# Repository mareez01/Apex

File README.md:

# Project Apex: Mixed-Signal Diagnostic Instrument

Hardware design, manufacturing files, and system architecture for Project Apex, a multi-functional diagnostic edge-computing tool

**Demonstration:**
*   Watch the hardware demo here: https://drive.google.com/drive/folders/1B4_CrYPebX7i6lBTUv4ibxBGYRtsgXC7?usp=sharing

## Version 1.0 (Current Files)
*   **Architecture:** Dual-MCU system featuring an ESP32 master and ATmega328P co-processor.
*   **PCB:** Custom 4-layer stackup engineered to ensure signal integrity by isolating the 3.3V digital logic from the 5V analog domains[cite: 1].
*   **Analog Front-End:** Auto-ranging 12-bit impedance analyzer utilizing an AD9833 waveform generator, MCP6022 PGA, and MCP3208 ADC over an isolated SPI bus.
*   **Digital IC Tester:** 16-pin ZIF socket routed via a discrete 1P3T mechanical switch matrix for deterministic fault injection and truth-table validation.
*   **Project reports are listed:** The Final version 1 project report have been submitted with all the ECAD files and GERBER files.

## Version 2.0 Roadmap (In Development)
Transitioning to a fully autonomous, solid-state architecture to support 24MSPS logic analysis and frequency response plotting (Bode/Nyquist).
*   **Master MCU:** Upgrading to STM32H723 (550MHz) utilizing DMA for high-speed ADC polling and 16-channel logic analysis.
*   **Slave MCU:** Upgrading to AVR32DB48. Utilizes native Multi-Voltage I/O (MVIO) on Port C to eliminate external level shifters. Includes dedicated 12-bit ADC channels for absolute floating-gate fault detection.
*   **Solid-State Matrix:** Replacing mechanical relays with an AO4606/SI1539CDL MOSFET crossbar switching matrix for automated IC power routing.
*   **PC Interface:** Transitioning from serial prints to a Python/PySide6 desktop GUI utilizing pySerial for live PyQtGraph data visualization.
*   **Design Files** So we are actively wroking on the version 2 deisgn and the design documention file is listed here please use iitm mail id to view the G-sheets :https://docs.google.com/document/d/17MV_ibkEd-tFQ1U5sWTHGYrbQkPEoYyiVjMqvgrKTJg/edit?usp=sharing

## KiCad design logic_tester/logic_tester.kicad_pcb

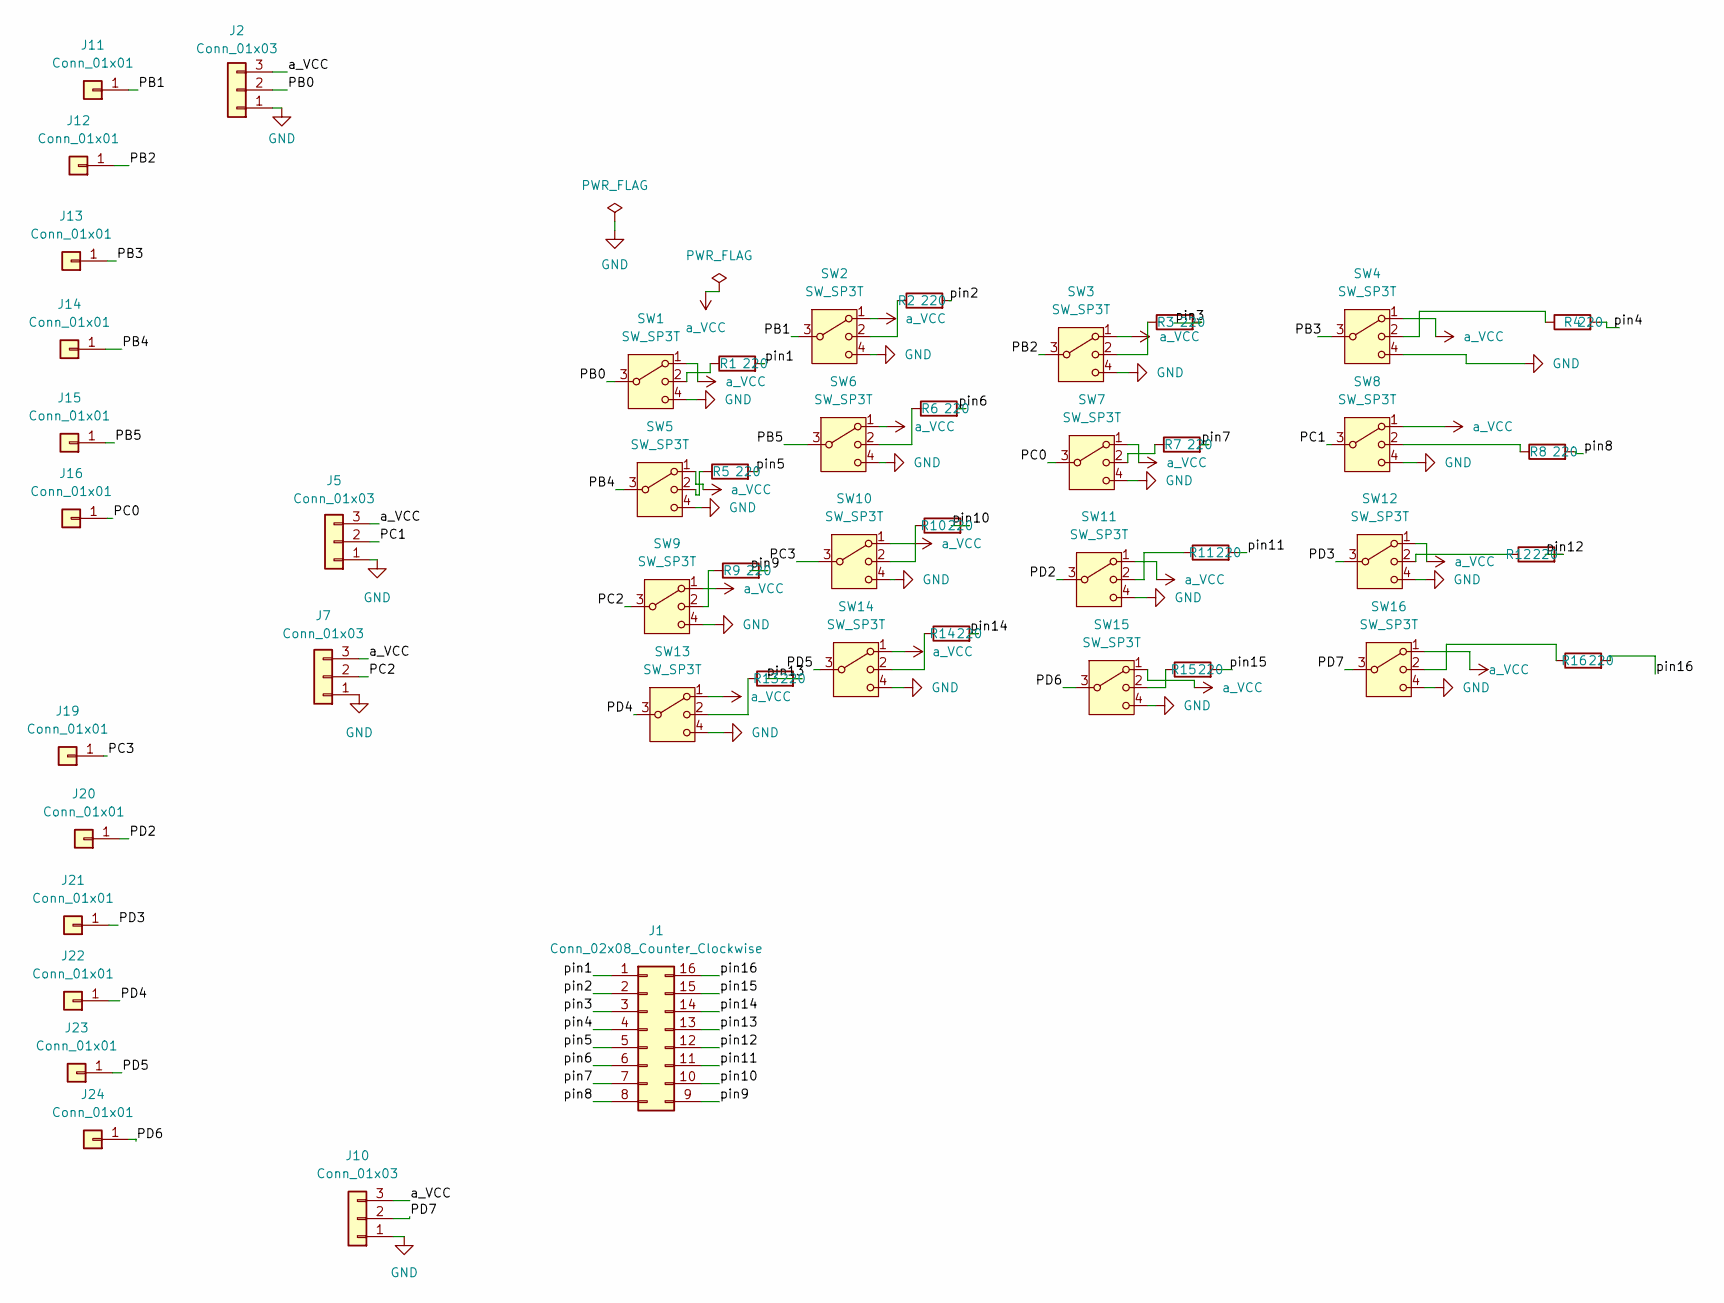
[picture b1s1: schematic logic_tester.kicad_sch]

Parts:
J1: Conn_02x08_Counter_Clockwise; DIP-16_W7.62mm_Socket_LongPads
J2, J5, J7, J10: Conn_01x03; PinSocket_1x03_P2.00mm_Vertical
J11, J12, J13, J14, J15: Conn_01x01; PinSocket_1x01_P2.54mm_Vertical
J16, J19, J20, J21, J22, J23, J24: Conn_01x01; PinSocket_1x01_P2.00mm_Vertical
R1, R2, R3, R4, R5, R6, R7, R8, R9, R10, R11, R12, R13, R14, R15, R16: 220; R_Axial_DIN0204_L3.6mm_D1.6mm_P7.62mm_Horizontal
SW1, SW2, SW3, SW4, SW5, SW6, SW7, SW8, SW9, SW10, SW11, SW12, SW13, SW14, SW15, SW16: SW_SP3T; SS13D07VG4_SHN

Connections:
/PB0: J2.2, SW1.3
/PB1: J11.1 (Pin_1_1), SW2.3
/PB2: J12.1 (Pin_1_1), SW3.3
/PB3: J13.1 (Pin_1_1), SW4.3
/PB4: J14.1 (Pin_1_1), SW5.3
/PB5: J15.1 (Pin_1_1), SW6.3
/PC0: J16.1 (Pin_1_1), SW7.3
/PC1: J5.2, SW8.3
/PC2: J7.2, SW9.3
/PC3: J19.1 (Pin_1_1), SW10.3
/PD2: J20.1 (Pin_1_1), SW11.3
/PD3: J21.1 (Pin_1_1), SW12.3
/PD4: J22.1 (Pin_1_1), SW13.3
/PD5: J23.1 (Pin_1_1), SW14.3
/PD6: J24.1 (Pin_1_1), SW15.3
/PD7: J10.2, SW16.3
/pin1: J1.1, R1.2
/pin2: J1.2, R2.2
/pin3: J1.3, R3.2
/pin4: J1.4, R4.2
/pin5: J1.5, R5.2
/pin6: J1.6, R6.2
/pin7: J1.7, R7.2
/pin8: J1.8, R8.2
/pin9: J1.9, R9.2
/pin10: J1.10, R10.2
/pin11: J1.11, R11.2
/pin12: J1.12, R12.2
/pin13: J1.13, R13.2
/pin14: J1.14, R14.2
/pin15: J1.15, R15.2
/pin16: J1.16, R16.2
GND: J2.1, J5.1, J7.1, J10.1, SW1.4, SW2.4, SW3.4, SW4.4, SW5.4, SW6.4, SW7.4, SW8.4, SW9.4, SW10.4, SW11.4, SW12.4, SW13.4, SW14.4, SW15.4, SW16.4
unnamed: R1.1, SW1.2
unnamed: R2.1, SW2.2
unnamed: R3.1, SW3.2
unnamed: R4.1, SW4.2
unnamed: R5.1, SW5.2
unnamed: R6.1, SW6.2
unnamed: R7.1, SW7.2
unnamed: R8.1, SW8.2
unnamed: R9.1, SW9.2
unnamed: R10.1, SW10.2
unnamed: R11.1, SW11.2
unnamed: R12.1, SW12.2
unnamed: R13.1, SW13.2
unnamed: R14.1, SW14.2
unnamed: R15.1, SW15.2
unnamed: R16.1, SW16.2
a_VCC: J2.3, J5.3, J7.3, J10.3, SW1.1, SW2.1, SW3.1, SW4.1, SW5.1, SW6.1, SW7.1, SW8.1, SW9.1, SW10.1, SW11.1, SW12.1, SW13.1, SW14.1, SW15.1, SW16.1

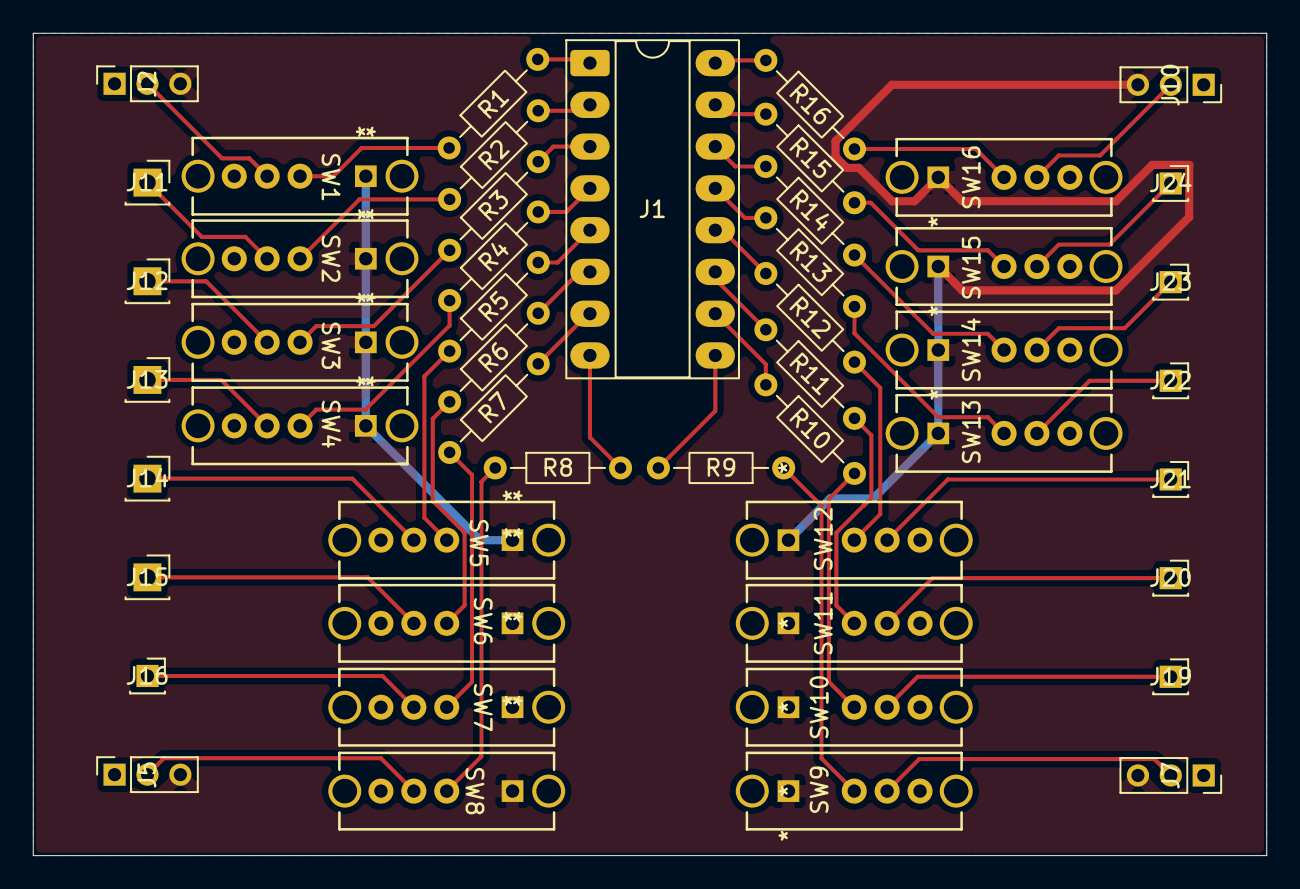
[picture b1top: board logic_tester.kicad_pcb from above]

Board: 2 copper layers, 75.0 x 50.0 mm, 49 parts (0 on the bottom side), 50 nets.

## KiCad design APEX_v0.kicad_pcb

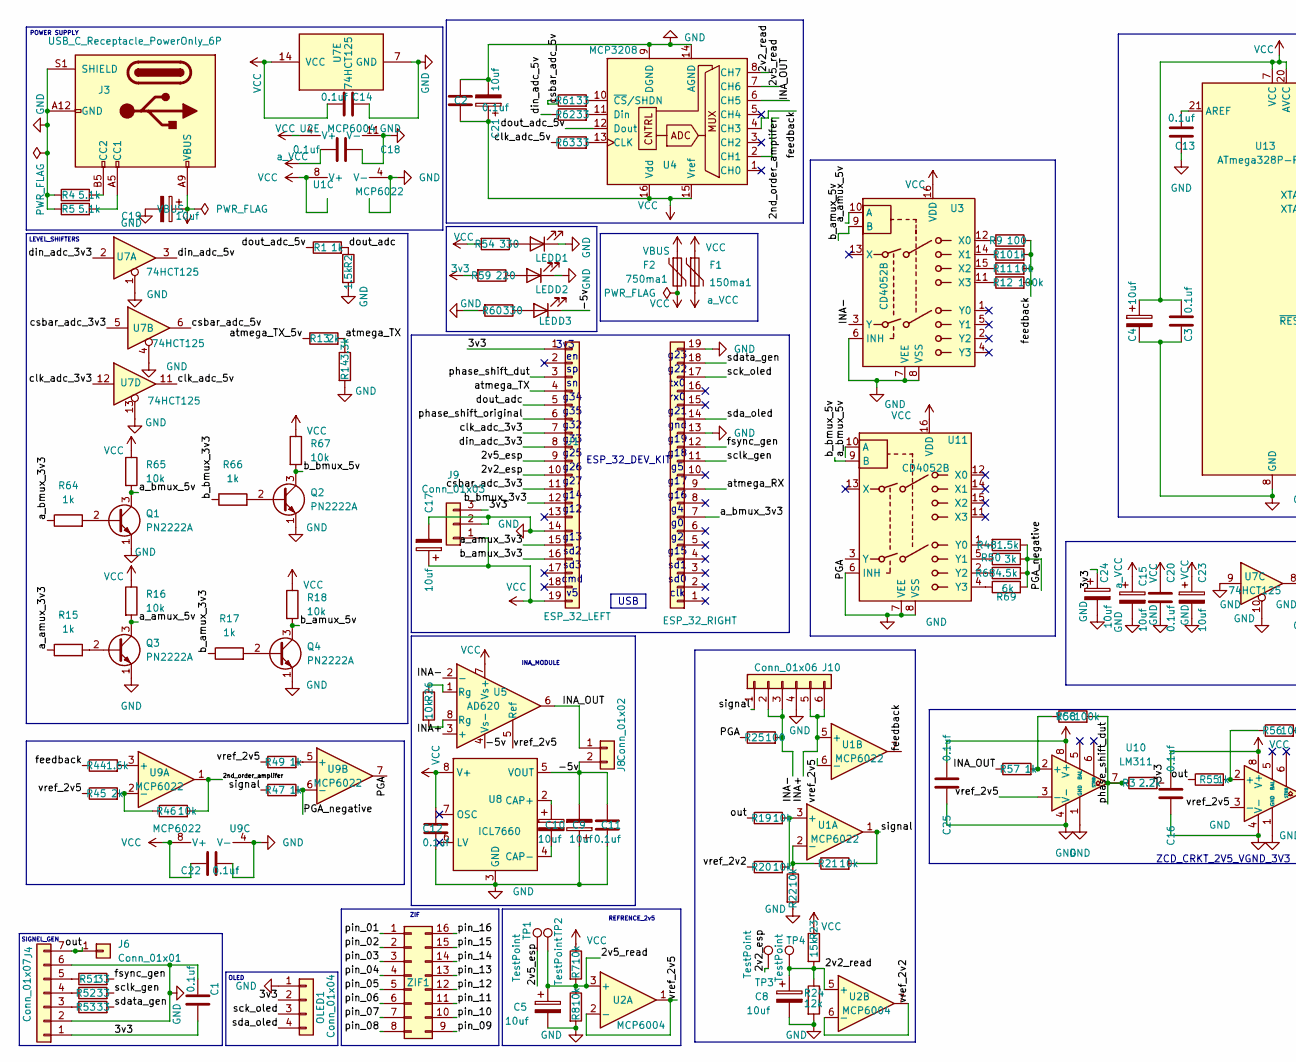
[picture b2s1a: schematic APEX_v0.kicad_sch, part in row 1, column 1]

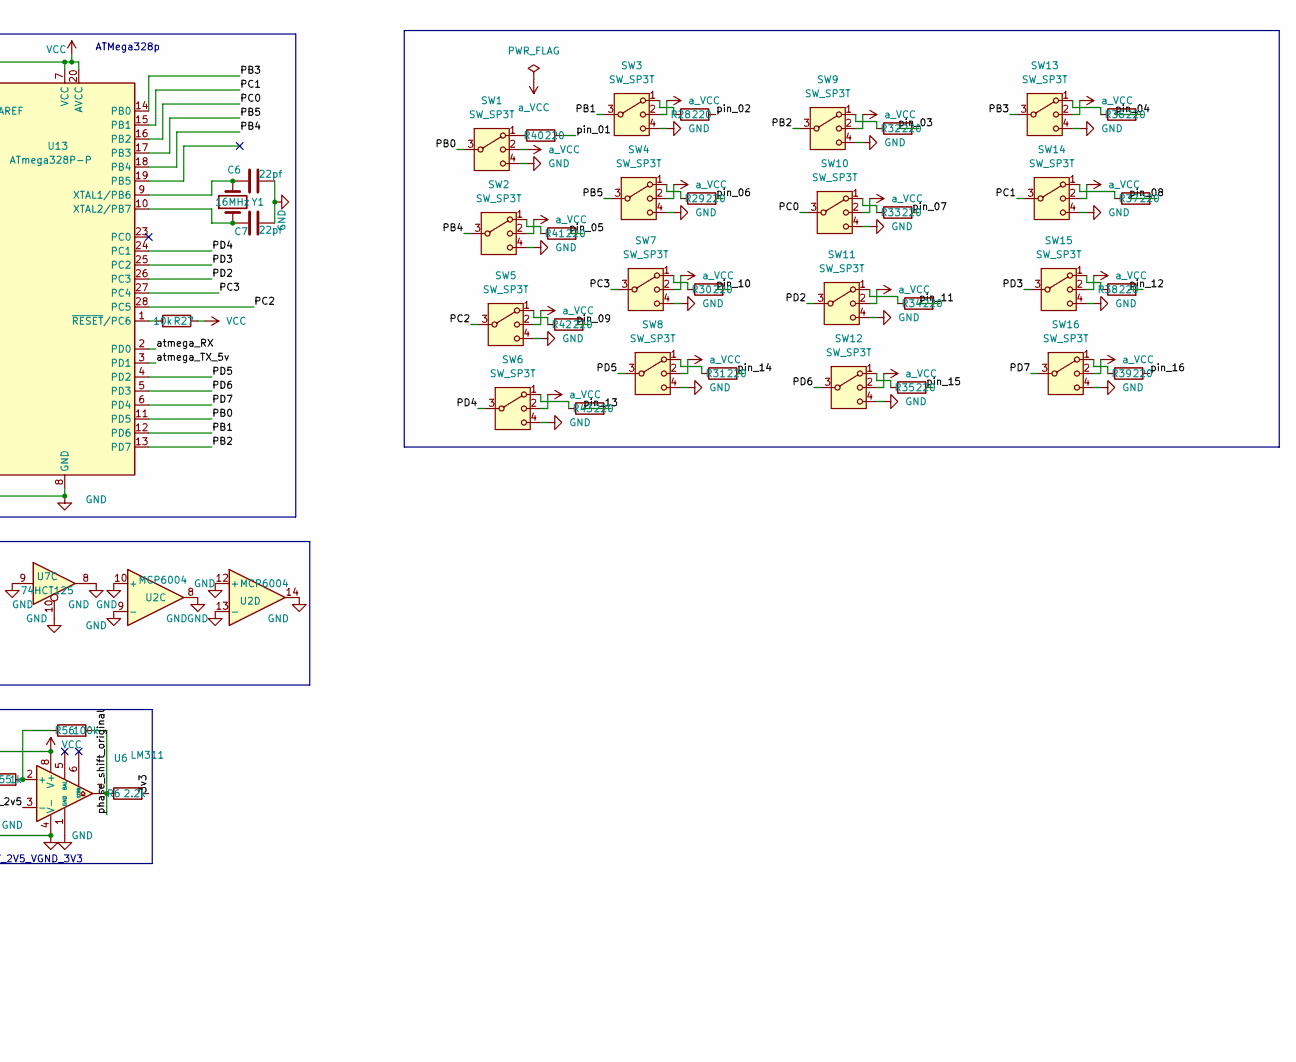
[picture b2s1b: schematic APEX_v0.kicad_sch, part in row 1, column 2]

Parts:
C1, C2, C3, C11, C12, C13, C14, C16, C18, C20, C22, C25: 0.1uf; C_Disc_D5.0mm_W2.5mm_P5.00mm
C4, C5, C8, C9, C10, C15, C17, C19, C21, C23, C24: 10uf; CP_Radial_D4.0mm_P2.00mm
C6, C7: 22pf; C_Disc_D5.0mm_W2.5mm_P5.00mm
D1, D2, D3: LED; LED_D3.0mm
F1: 150ma1; R_Axial_DIN0204_L3.6mm_D1.6mm_P7.62mm_Horizontal
F2: 750ma1; R_Axial_DIN0204_L3.6mm_D1.6mm_P7.62mm_Horizontal
J1: ESP_32_LEFT; PinSocket_1x19_P2.54mm_Vertical
J2: ESP_32_RIGHT; PinSocket_1x19_P2.54mm_Vertical
J3: USB_C_Receptacle_PowerOnly_6P; USB_C_Receptacle_GCT_USB4135-GF-A_6P_TopMnt_Horizontal
J4: Conn_01x07; PinSocket_1x07_P2.54mm_Vertical
J6: Conn_01x01; PinSocket_1x01_P2.54mm_Vertical
J8: Conn_01x02; PinSocket_1x02_P2.54mm_Vertical
J9: Conn_01x03; PinSocket_1x03_P2.54mm_Vertical
J10: Conn_01x06; PinSocket_1x06_P2.54mm_Vertical
OLED1: Conn_01x04; PinSocket_1x04_P2.54mm_Vertical
Q1, Q2, Q3, Q4: PN2222A; TO-92_Inline
R1, R10, R15, R17, R47, R49, R55, R57, R64, R66: 1k; R_Axial_DIN0204_L3.6mm_D1.6mm_P7.62mm_Horizontal
R2, R48: 1.5k; R_Axial_DIN0204_L3.6mm_D1.6mm_P7.62mm_Horizontal
R3, R6: 2.2k; R_Axial_DIN0204_L3.6mm_D1.6mm_P7.62mm_Horizontal
R4, R5: 5.1k; R_Axial_DIN0204_L3.6mm_D1.6mm_P7.62mm_Horizontal
R7, R8, R11, R16, R18, R19, R20, R21, R22, R26, R27, R46, R65, R67: 10k; R_Axial_DIN0204_L3.6mm_D1.6mm_P7.62mm_Horizontal
R9, R25: 100; R_Axial_DIN0204_L3.6mm_D1.6mm_P7.62mm_Horizontal
R12, R56, R58: 100k; R_Axial_DIN0204_L3.6mm_D1.6mm_P7.62mm_Horizontal
R13, R45: 2k; R_Axial_DIN0204_L3.6mm_D1.6mm_P7.62mm_Horizontal
R14: 3.3k; R_Axial_DIN0204_L3.6mm_D1.6mm_P7.62mm_Horizontal
R23: 15k; R_Axial_DIN0204_L3.6mm_D1.6mm_P7.62mm_Horizontal
R24: 12k; R_Axial_DIN0204_L3.6mm_D1.6mm_P7.62mm_Horizontal
R28, R29, R30, R31, R32, R33, R34, R35, R36, R37, R38, R39, R40, R41, R42, R43, R59: 220; R_Axial_DIN0204_L3.6mm_D1.6mm_P7.62mm_Horizontal
R44: 1.6k; R_Axial_DIN0204_L3.6mm_D1.6mm_P7.62mm_Horizontal
R50: 3k; R_Axial_DIN0204_L3.6mm_D1.6mm_P7.62mm_Horizontal
R51, R52, R53, R61, R62, R63: 33; R_Axial_DIN0204_L3.6mm_D1.6mm_P7.62mm_Horizontal
R54, R60: 330; R_Axial_DIN0204_L3.6mm_D1.6mm_P7.62mm_Horizontal
R68: 4.5k; R_Axial_DIN0204_L3.6mm_D1.6mm_P7.62mm_Horizontal
R69: 6k; R_Axial_DIN0204_L3.6mm_D1.6mm_P7.62mm_Horizontal
SW1, SW2, SW3, SW4, SW5, SW6, SW7, SW8, SW9, SW10, SW11, SW12, SW13, SW14, SW15, SW16: SW_SP3T; SS13D07VG4_SHN
TP1, TP2, TP3, TP4: TestPoint; TestPoint_Pad_D1.0mm
U1, U9: MCP6022; DIP-8_W7.62mm_Socket_LongPads
U2: MCP6004; DIP-14_W7.62mm_Socket
U3, U11: CD4052B; DIP-16_W7.62mm_Socket_LongPads
U4: MCP3208; DIP-16_W7.62mm_Socket_LongPads
U5: AD620; DIP-8_W7.62mm_Socket_LongPads
U6, U10: LM311; DIP-8_W7.62mm_Socket_LongPads
U7: 74HCT125; DIP-14_W7.62mm_Socket_LongPads
U8: ICL7660; DIP-8_W7.62mm_Socket_LongPads
U13: ATmega328P-P; DIP-28_W7.62mm_Socket_LongPads
Y1: 16MHz; Crystal_HC49-U_Vertical
ZIF1: DIP-16_W7.62mm_Socket_LongPads

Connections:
3v3: C1.1, C24.1, J1.1, J4.1, J9.3, OLED1.2, R3.2, R6.2, R59.2
/2nd_order_amplifer: R46.2, U4.2 (CH1), U9.1
/2v2_esp: J1.10, TP3.1 (1_1)
/2v2_read: C8.1, R23.2, R24.1, TP4.1 (1_1), U2.5 (+), U4.8 (CH7)
/2v5_esp: J1.9, TP1.1 (1_1)
/2v5_read: C5.1, R7.2, R8.1, TP2.1 (1_1), U2.3 (+), U4.7 (CH6)
/-5v: C9.2, C11.1, D3.1 (K), J8.2, U5.4 (Vs-), U8.5 (VOUT)
/INA+: J10.5, J10.6, U1.5 (+), U5.3 (+)
/INA-: J10.2, J10.3, R25.2, U3.3 (Y), U5.2 (-)
/INA_OUT: J8.1, R57.1, U4.6 (CH5), U5.6
/PB0: SW1.3, U13.11 (PD5)
/PB1: SW3.3, U13.12 (PD6)
/PB2: SW9.3, U13.13 (PD7)
/PB3: SW13.3, U13.14 (PB0)
/PB4: SW2.3, U13.18 (PB4)
/PB5: SW4.3, U13.17 (PB3)
/PC0: SW10.3, U13.16 (PB2)
/PC1: SW14.3, U13.15 (PB1)
/PC2: SW5.3, U13.28 (PC5)
/PC3: SW7.3, U13.27 (PC4)
/PD2: SW11.3, U13.26 (PC3)
/PD3: SW15.3, U13.25 (PC2)
/PD4: SW6.3, U13.24 (PC1)
/PD5: SW8.3, U13.4 (PD2)
/PD6: SW12.3, U13.5 (PD3)
/PD7: SW16.3, U13.6 (PD4)
/PGA: R25.1, U9.7, U11.3 (Y)
/PGA_negative: R47.2, R48.1, R50.2, R68.2, R69.2, U9.6 (-)
/a_amux_3v3: J1.15, R15.1
/a_amux_5v: Q3.3 (C), R16.2, U3.10 (A)
/a_bmux_3v3: J2.7, R64.1
/a_bmux_5v: Q1.3 (C), R65.2, U11.10 (A)
/atmega_RX: J2.9, U13.2 (PD0)
/atmega_TX: J1.4, R13.2, R14.1
/atmega_TX_5v: R13.1, U13.3 (PD1)
/b_amux_3v3: J1.16, R17.1
/b_amux_5v: Q4.3 (C), R18.2, U3.9 (B)
/b_bmux_3v3: J1.12, R66.1
/b_bmux_5v: Q2.3 (C), R67.2, U11.9 (B)
/clk_adc_3v3: J1.7, U7.12
/clk_adc_5v: R63.1, U7.11
/csbar_adc_3v3: J1.11, U7.5
/csbar_adc_5v: R61.1, U7.6
/din_adc_3v3: J1.8, U7.2
/din_adc_5v: R62.1, U7.3
/dout_adc: J1.5, R1.2, R2.1
/dout_adc_5v: R1.1, U4.12 (Dout)
/feedback: R9.2, R10.2, R11.2, R12.2, R44.1, U1.7, U4.4 (CH3)
/fsync_gen: J2.12, R51.2
/out: J4.7, J6.1 (Pin_1_1), R19.1, R55.1
/phase_shift_dut: J1.3, R3.1, R58.2, U10.7
/phase_shift_original: J1.6, R6.1, R56.2, U6.7
/pin_01: R40.2, ZIF1.1
/pin_02: R28.2, ZIF1.2
/pin_03: R32.2, ZIF1.3
/pin_04: R36.2, ZIF1.4
/pin_05: R41.2, ZIF1.5
/pin_06: R29.2, ZIF1.6
/pin_07: R33.2, ZIF1.7
/pin_08: R37.2, ZIF1.8
/pin_09: R42.2, ZIF1.9
/pin_10: R30.2, ZIF1.10
/pin_11: R34.2, ZIF1.11
/pin_12: R38.2, ZIF1.12
/pin_13: R43.2, ZIF1.13
/pin_14: R31.2, ZIF1.14
/pin_15: R35.2, ZIF1.15
/pin_16: R39.2, ZIF1.16
/sck_oled: J2.17, OLED1.3
/sclk_gen: J2.11, R52.2
/sda_oled: J2.14, OLED1.4
/sdata_gen: J2.18, R53.2
/signal: J10.1, R21.2, R47.1, U1.1
/vref_2v2: R20.1, U2.6 (-), U2.7
/vref_2v5: R45.1, R49.1, U1.6 (-), U2.1, U2.2 (-), U5.5 (Ref), U6.3 (-), U10.3 (-)
GND: C1.2, C2.1, C3.2, C4.2, C5.2, C6.2, C7.2, C8.2, C9.1, C11.2, C12.2, C13.2, C14.2, C15.2, C16.2, C17.2, C18.2, C19.2, C20.2, C21.2, C22.2, C23.2, C24.2, C25.2, D1.1 (K), D2.1 (K), J1.14, J2.13, J2.19, J3.A12 (GND), J3.B12 (GND), J3.S1 (SHIELD), J4.2, J4.6, J9.2, J10.4, OLED1.1, Q1.1 (E), Q2.1 (E), Q3.1 (E), Q4.1 (E), R2.2, R4.1, R5.1, R8.2, R14.2, R22.2, R24.2, R60.2, SW1.4, SW2.4, SW3.4, SW4.4, SW5.4, SW6.4, SW7.4, SW8.4, SW9.4, SW10.4, SW11.4, SW12.4, SW13.4, SW14.4, SW15.4, SW16.4, U1.4 (V-), U2.8, U2.9 (-), U2.10 (+), U2.11 (V-), U2.12 (+), U2.13 (-), U2.14, U3.6 (INH), U3.7 (VEE), U3.8 (VSS), U4.9 (DGND), U4.14 (AGND), U6.1 (GND), U6.4 (V-), U7.1, U7.4, U7.7 (GND), U7.8, U7.9, U7.10, U7.13, U8.3 (GND), U9.4 (V-), U10.1 (GND), U10.4 (V-), U11.6 (INH), U11.7 (VEE), U11.8 (VSS), U13.8 (GND), U13.22 (GND)
unnamed: D1.2 (A), R54.1
unnamed: D2.2 (A), R59.1
unnamed: D3.2 (A), R60.1
unnamed: J3.A5 (CC1), R5.2
unnamed: J3.B5 (CC2), R4.2
unnamed: J4.3, R53.1
unnamed: J4.4, R52.1
unnamed: J4.5, R51.1
unnamed: Q1.2 (B), R64.2
unnamed: Q2.2 (B), R66.2
unnamed: Q3.2 (B), R15.2
unnamed: Q4.2 (B), R17.2
unnamed: R26.1, U5.1 (Rg)
unnamed: R26.2, U5.8 (Rg)
unnamed: R28.1, SW3.1
unnamed: R29.1, SW4.1
unnamed: R30.1, SW7.1
unnamed: R31.1, SW8.1
unnamed: R32.1, SW9.1
unnamed: R33.1, SW10.1
unnamed: R34.1, SW11.1
unnamed: R35.1, SW12.1
unnamed: R36.1, SW13.1
unnamed: R37.1, SW14.1
unnamed: R38.1, SW15.1
unnamed: R39.1, SW16.1
unnamed: R40.1, SW1.1
unnamed: R41.1, SW2.1
unnamed: R42.1, SW5.1
unnamed: R43.1, SW6.1
unnamed: R19.2, R20.2, U1.3 (+)
unnamed: R21.1, R22.1, U1.2 (-)
unnamed: R9.1, U3.12 (X0)
unnamed: R10.1, U3.14 (X1)
unnamed: R11.1, U3.15 (X2)
unnamed: R12.1, U3.11 (X3)
unnamed: R63.2, U4.13 (CLK)
unnamed: R62.2, U4.11 (Din)
unnamed: R61.2, U4.10 (~CS/SHDN)
unnamed: R55.2, R56.1, U6.2 (+)
unnamed: C10.1, U8.2 (CAP+)
unnamed: C10.2, U8.4 (CAP-)
unnamed: R44.2, U9.3 (+)
unnamed: R45.2, R46.1, U9.2 (-)
unnamed: R49.2, U9.5 (+)
unnamed: R57.2, R58.1, U10.2 (+)
unnamed: R48.2, U11.1 (Y0)
unnamed: R50.1, U11.5 (Y1)
unnamed: R68.1, U11.2 (Y2)
unnamed: R69.1, U11.4 (Y3)
unnamed: C13.1, U13.21 (AREF)
unnamed: C6.1, U13.9 (XTAL1/PB6), Y1.2
unnamed: C7.1, U13.10 (XTAL2/PB7), Y1.1
unnamed: R27.2, U13.1 (~RESET/PC6)
VBUS: C19.1, F2.1, J3.A9 (VBUS), J3.B9 (VBUS)
VCC: C2.2, C3.1, C4.1, C12.1, C14.1, C16.1, C17.1, C20.1, C21.1, C22.1, C23.1, C25.1, F1.1, F2.2, J1.19, J9.1, R7.1, R16.1, R18.1, R23.1, R27.1, R54.2, R65.1, R67.1, U1.8 (V+), U2.4 (V+), U3.16 (VDD), U4.15 (Vref), U4.16 (Vdd), U5.7 (Vs+), U6.8 (V+), U7.14 (VCC), U8.8 (V+), U9.8 (V+), U10.8 (V+), U11.16 (VDD), U13.7 (VCC), U13.20 (AVCC)
a_VCC: C15.1, C18.1, F1.2, SW1.2, SW2.2, SW3.2, SW4.2, SW5.2, SW6.2, SW7.2, SW8.2, SW9.2, SW10.2, SW11.2, SW12.2, SW13.2, SW14.2, SW15.2, SW16.2

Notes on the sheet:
3v3
ZCD_CRKT_2V5_VGND_3V3
g17
sd0
INA_MODULE
g16
SIGNEL_GEN
g18
OLED
sd1
g22
g27
g23
sd2
g15
g14
g13
g35
g25
g33
tx0
rx0
g12
g26
clk
POWER SUPPLY
USB
g19
ATMega328p
gnd
LEVEL_SHIFTERS
REFRENCE_2v5
g34
sd3
g21
cmd
g32
ESP_32_DEV_KIT
ZIF

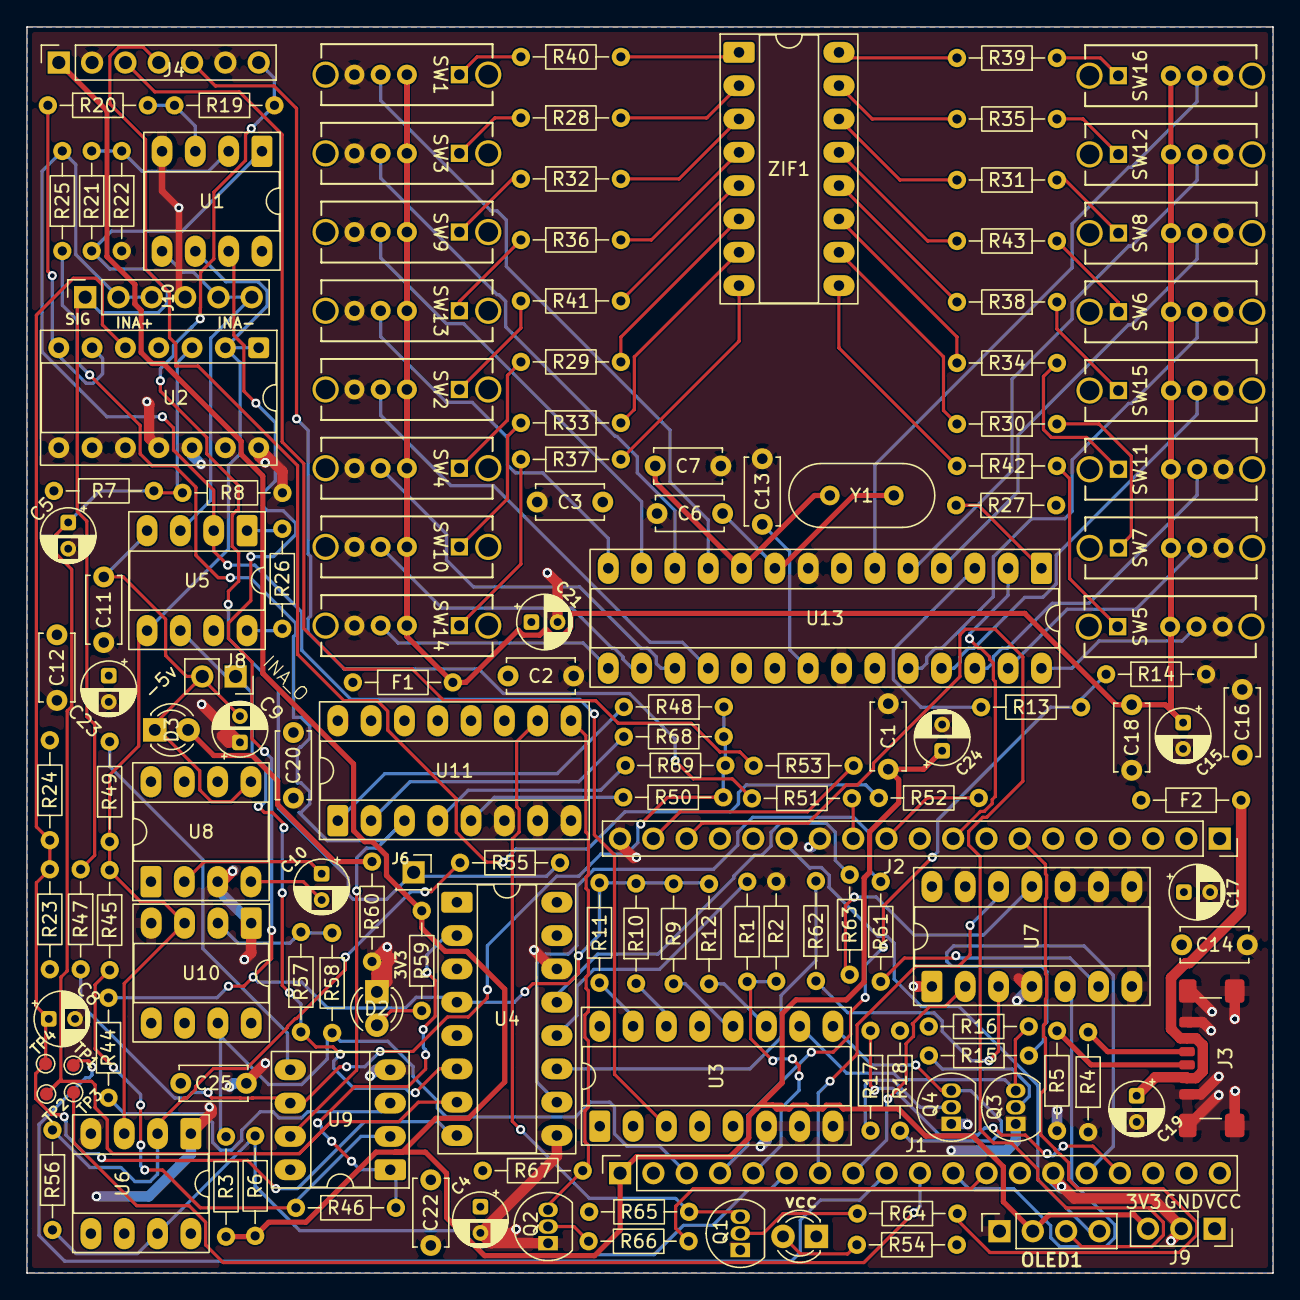
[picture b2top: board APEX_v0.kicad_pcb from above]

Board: 4 copper layers, 95.0 x 95.0 mm, 146 parts (0 on the bottom side), 133 nets.

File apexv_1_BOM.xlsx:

Reference | Qty | Value | DNP | Exclude from BOM | Exclude from Board | Footprint | Datasheet
C1,C2,C3,C11,C12,C13,C14,C16,C18,C20,C22,C25 | 12 | 0.1uf |  |  |  | Capacitor_THT:C_Disc_D5.0mm_W2.5mm_P5.00mm | ~
C4,C5,C8,C9,C10,C15,C17,C19,C21,C23,C24 | 11 | 10uf |  |  |  | Capacitor_THT:CP_Radial_D4.0mm_P2.00mm | ~
C6,C7 | 2 | 22pf |  |  |  | Capacitor_THT:C_Disc_D5.0mm_W2.5mm_P5.00mm | ~
D1,D2,D3 | 3 | LED |  |  |  | LED_THT:LED_D3.0mm | ~
F1 | 1 | 150ma1 |  |  |  | Resistor_THT:R_Axial_DIN0204_L3.6mm_D1.6mm_P7.62mm_Horizontal | ~
F2 | 1 | 750ma1 |  |  |  | Resistor_THT:R_Axial_DIN0204_L3.6mm_D1.6mm_P7.62mm_Horizontal | ~
J1 | 1 | ESP_32_LEFT |  |  |  | Connector_PinSocket_2.54mm:PinSocket_1x19_P2.54mm_Vertical | ~
J2 | 1 | ESP_32_RIGHT |  |  |  | Connector_PinSocket_2.54mm:PinSocket_1x19_P2.54mm_Vertical | ~
J3 | 1 | USB_C_Receptacle_PowerOnly_6P |  |  |  | Connector_USB:USB_C_Receptacle_GCT_USB4135-GF-A_6P_TopMnt_Horizontal | https://www.usb.org/sites/default/files/documents/usb_type-c.zip
J4 | 1 | Conn_01x07 |  |  |  | Connector_PinSocket_2.54mm:PinSocket_1x07_P2.54mm_Vertical | ~
J6 | 1 | Conn_01x01 |  |  |  | Connector_PinSocket_2.54mm:PinSocket_1x01_P2.54mm_Vertical | ~
J8 | 1 | Conn_01x02 |  |  |  | Connector_PinSocket_2.54mm:PinSocket_1x02_P2.54mm_Vertical | ~
J9 | 1 | Conn_01x03 |  |  |  | Connector_PinSocket_2.54mm:PinSocket_1x03_P2.54mm_Vertical | ~
J10 | 1 | Conn_01x06 |  |  |  | Connector_PinSocket_2.54mm:PinSocket_1x06_P2.54mm_Vertical | ~
OLED1 | 1 | Conn_01x04 |  |  |  | Connector_PinSocket_2.54mm:PinSocket_1x04_P2.54mm_Vertical | ~
Q1,Q2,Q3,Q4 | 4 | PN2222A |  |  |  | Package_TO_SOT_THT:TO-92_Inline | https://www.onsemi.com/pub/Collateral/PN2222-D.PDF
R1,R10,R15,R17,R47,R49,R55,R57,R64,R66 | 10 | 1k |  |  |  | Resistor_THT:R_Axial_DIN0204_L3.6mm_D1.6mm_P7.62mm_Horizontal | ~
R2,R48 | 2 | 1.5k |  |  |  | Resistor_THT:R_Axial_DIN0204_L3.6mm_D1.6mm_P7.62mm_Horizontal | ~
R3,R6 | 2 | 2.2k |  |  |  | Resistor_THT:R_Axial_DIN0204_L3.6mm_D1.6mm_P7.62mm_Horizontal | ~
R4,R5 | 2 | 5.1k |  |  |  | Resistor_THT:R_Axial_DIN0204_L3.6mm_D1.6mm_P7.62mm_Horizontal | ~
R7,R8,R11,R16,R18,R19,R20,R21,R22,R26,R27,R46,R65,R67 | 14 | 10k |  |  |  | Resistor_THT:R_Axial_DIN0204_L3.6mm_D1.6mm_P7.62mm_Horizontal | ~
R9,R25 | 2 | 100 |  |  |  | Resistor_THT:R_Axial_DIN0204_L3.6mm_D1.6mm_P7.62mm_Horizontal | ~
R12,R56,R58 | 3 | 100k |  |  |  | Resistor_THT:R_Axial_DIN0204_L3.6mm_D1.6mm_P7.62mm_Horizontal | ~
R13,R45 | 2 | 2k |  |  |  | Resistor_THT:R_Axial_DIN0204_L3.6mm_D1.6mm_P7.62mm_Horizontal | ~
R14 | 1 | 3.3k |  |  |  | Resistor_THT:R_Axial_DIN0204_L3.6mm_D1.6mm_P7.62mm_Horizontal | ~
R23 | 1 | 15k |  |  |  | Resistor_THT:R_Axial_DIN0204_L3.6mm_D1.6mm_P7.62mm_Horizontal | ~
R24 | 1 | 12k |  |  |  | Resistor_THT:R_Axial_DIN0204_L3.6mm_D1.6mm_P7.62mm_Horizontal | ~
R28,R29,R30,R31,R32,R33,R34,R35,R36,R37,R38,R39,R40,R41,R42,R43,R59 | 17 | 220 |  |  |  | Resistor_THT:R_Axial_DIN0204_L3.6mm_D1.6mm_P7.62mm_Horizontal | ~
R44 | 1 | 1.6k |  |  |  | Resistor_THT:R_Axial_DIN0204_L3.6mm_D1.6mm_P7.62mm_Horizontal | ~
R50 | 1 | 3k |  |  |  | Resistor_THT:R_Axial_DIN0204_L3.6mm_D1.6mm_P7.62mm_Horizontal | ~
R51,R52,R53 | 3 | 22 |  |  |  | Resistor_THT:R_Axial_DIN0204_L3.6mm_D1.6mm_P7.62mm_Horizontal | ~
R54,R60 | 2 | 330 |  |  |  | Resistor_THT:R_Axial_DIN0204_L3.6mm_D1.6mm_P7.62mm_Horizontal | ~
R61,R62,R63 | 3 | 33 |  |  |  | Resistor_THT:R_Axial_DIN0204_L3.6mm_D1.6mm_P7.62mm_Horizontal | ~
R68 | 1 | 4.5k |  |  |  | Resistor_THT:R_Axial_DIN0204_L3.6mm_D1.6mm_P7.62mm_Horizontal | ~
R69 | 1 | 6k |  |  |  | Resistor_THT:R_Axial_DIN0204_L3.6mm_D1.6mm_P7.62mm_Horizontal | ~
SW1,SW2,SW3,SW4,SW5,SW6,SW7,SW8,SW9,SW10,SW11,SW12,SW13,SW14,SW15,SW16 | 16 | SW_SP3T |  |  |  | SP3T:SS13D07VG4_SHN | ~
TP1,TP2,TP3,TP4 | 4 | TestPoint |  |  |  | TestPoint:TestPoint_Pad_D1.0mm | ~
U1,U9 | 2 | MCP6022 |  |  |  | Package_DIP:DIP-8_W7.62mm_Socket_LongPads | http://ww1.microchip.com/downloads/en/devicedoc/20001685e.pdf
U2 | 1 | MCP6004 |  |  |  | Package_DIP:DIP-14_W7.62mm_Socket | http://ww1.microchip.com/downloads/en/DeviceDoc/21733j.pdf
U3,U11 | 2 | CD4052B |  |  |  | Package_DIP:DIP-16_W7.62mm_Socket_LongPads | http://www.ti.com/lit/ds/symlink/cd4052b.pdf
U4 | 1 | MCP3208 |  |  |  | Package_DIP:DIP-16_W7.62mm_Socket_LongPads | http://ww1.microchip.com/downloads/en/DeviceDoc/21298c.pdf
U5 | 1 | AD620 |  |  |  | Package_DIP:DIP-8_W7.62mm_Socket_LongPads | https://www.analog.com/media/en/technical-documentation/data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
U6,U10 | 2 | LM311 |  |  |  | Package_DIP:DIP-8_W7.62mm_Socket_LongPads | https://www.st.com/resource/en/datasheet/lm311.pdf
U7 | 1 | 74HCT125 |  |  |  | Package_DIP:DIP-14_W7.62mm_Socket_LongPads | http://www.ti.com/lit/gpn/sn74LS125
U8 | 1 | ICL7660 |  |  |  | Package_DIP:DIP-8_W7.62mm_Socket_LongPads | http://datasheets.maximintegrated.com/en/ds/ICL7660-MAX1044.pdf
U13 | 1 | ATmega328P-P |  |  |  | Package_DIP:DIP-28_W7.62mm_Socket_LongPads | http://ww1.microchip.com/downloads/en/DeviceDoc/ATmega328_P%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
Y1 | 1 | 16MHz |  |  |  | Crystal:Crystal_HC49-U_Vertical | ~
ZIF1 | 1 | ~ |  |  |  | Package_DIP:DIP-16_W7.62mm_Socket_LongPads | ~
